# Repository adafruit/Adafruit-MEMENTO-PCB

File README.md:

## Adafruit MEMENTO - Python Programmable DIY Camera PCB

<a href="http://www.adafruit.com/products/5420"><br/>
Click here to purchase one from the Adafruit shop</a>

PCB files for the Adafruit MEMENTO - Python Programmable DIY Camera. 

Format is EagleCAD schematic and board layout
* https://www.adafruit.com/product/5420

### Description

Make memories, or just a cool camera-based project, with Adafruit's MEMENTO Camera Board. It's a development board with everything you need to create programmable camera and vision projects: with a camera module, TFT preview screen, buttons, SD card slot and driven by a powerful ESP32-S3 with 2 MB of PSRAM for buffering 5 MegaPixel camera images.

This product is just the mainboard, and does not come with an enclosure, LED ring, hardware, SD card, or battery.

The ESP32-S3 is a WiFi and Bluetooth LE capable, 240 MHz dual core Tensilica processor - much like the famous ESP32. The S3 adds native USB support so it's great for use with Arduino or CircuitPython. The S3 also has the ability to interface with raw camera modules. The cameras require 12 GPIO pins and fast data transfer in order to get images off the sensor, and then a lot of memory for storing 2560 x 1920 images - which is why we picked an S3 module with 2MB of PSRAM so that we can read JPEGs into memory for saving onto an SD card.

To make the board easy to use we added a ton of supporting hardware, here's a full list of the hardware included:

* ESP32-S3 module with 8 MB Flash, 2 MB PSRAM - dual core 240MHz Tensilica with WiFi and BTLE.
* OV5640 camera module with 72 degree view and auto-focus motor - 5MP camera sensor with JPEG encoder built in.
* 1.54" 240x240 Color TFT - For previewing the camera images, or user interface design.
* MicroSD card slot - Store images or animations to any SPI-capable micro SD card.
* Two Digital/Analog Stemma Ports - JST PH-3 connectors for A0, A1 and power+ground for adding external buttons, LEDs, or sensors. Can provide 3V or 5V power.
* I2C Stemma QT Port - Connect just about any I2C sensor you please with a Stemma QT JST SH port, provides 3.3V power and logic.
* LIS3DH Accelerometer - Triple-access accelerometer can detect orientation, shaking or movement.
* LiPoly battery charging support - Use a 3.7/4.2V 350mA or 420mA battery for on-the-go snaps.
* 6 User Buttons - change modes, preview saved images, play DOOM (?). Connected through a GPIO expander
* Buzzer - play tones or alerts, or indicate when a photo was successfully taken
* Analog Microphone - Can be used as a sensor to detect loud sounds, not for recording video with audio.
* Shutter button - Connected to GPIO 0 for entering the ROM bootloader
* Reset button - For entering the bootloader or starting over
* On/Off switch - Cut all power when using a battery 
* USB Type C for programming the ESP32-S3, as well as REPL access in CircuitPython and charging the optional LiPoly battery
* Breakout pads for hardware UART - for more intense debugging needs, solder wires to the through-hole pads to connect to a console cable.
* Four M3 standoffs for mounting or enclosure attachment.

We've got both Arduino and CircuitPython example code that lets you preview the camera, adjust settings, and take photos that are saved to disk. However, we recommend CircuitPython because the compilation time in Arduino is pretty intense due to the huge amount of code required to run the camera. CircuitPython is fast to develop for and our library will make it easy to start making custom camera projects.

### License

Adafruit invests time and resources providing this open source design, please support Adafruit and open-source hardware by purchasing products from [Adafruit](https://www.adafruit.com)!

Designed by Limor Fried/Ladyada for Adafruit Industries.

Creative Commons Attribution/Share-Alike, all text above must be included in any redistribution. 
See license.txt for additional details.

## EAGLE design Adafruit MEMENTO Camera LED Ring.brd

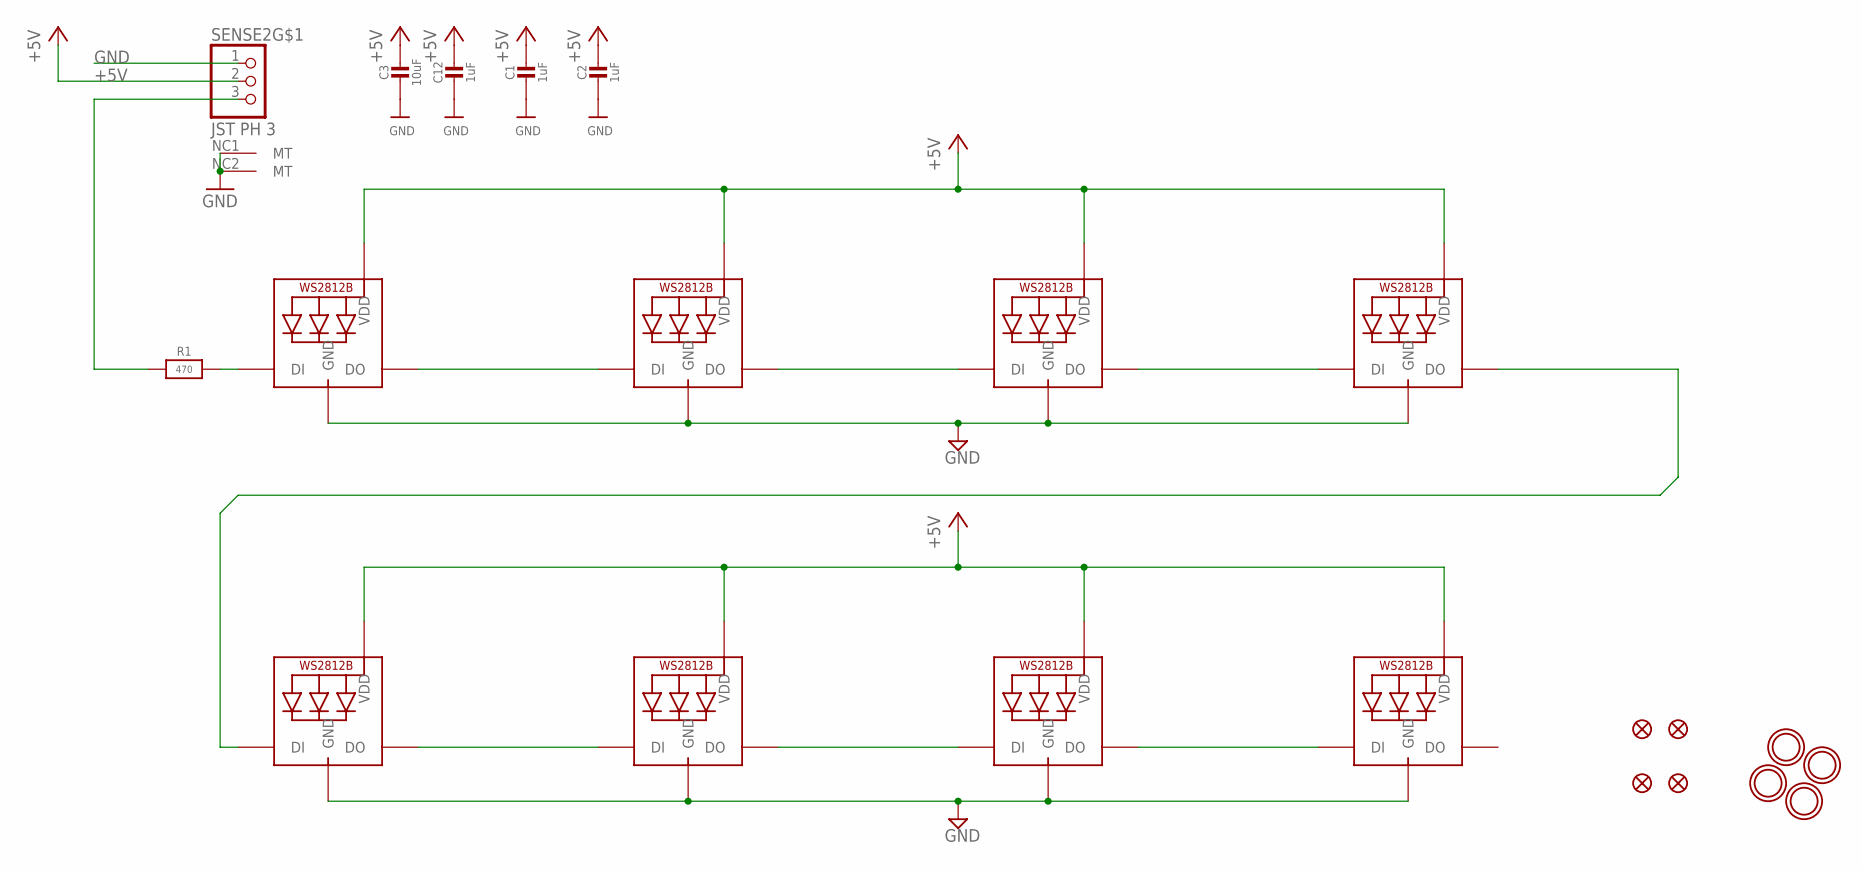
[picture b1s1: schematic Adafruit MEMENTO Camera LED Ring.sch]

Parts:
C1, C2, C12: 1uF; 0603-NO
C3: 10uF; 0805-NO
FID1, FID2, FID3, FID4: FIDUCIAL_1MM
LED1, LED3, LED5, LED7, LED9, LED11, LED13, LED15: WS2812B_5050N; WS2812B-NARROW
R1: 470; 0603-NO
SENSE2: JST PH 3; JSTPH3
U$1, U$2, U$3, U$4: MOUNTINGHOLE3.0THIN; MOUNTINGHOLE_3.0_PLATEDTHIN

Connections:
+5V: C1.1, C2.1, C3.1, C12.1, LED1.1-VDD (VDD), LED3.1-VDD (VDD), LED5.1-VDD (VDD), LED7.1-VDD (VDD), LED9.1-VDD (VDD), LED11.1-VDD (VDD), LED13.1-VDD (VDD), LED15.1-VDD (VDD), SENSE2.2
GND: C1.2, C2.2, C3.2, C12.2, LED1.3-GND (GND), LED3.3-GND (GND), LED5.3-GND (GND), LED7.3-GND (GND), LED9.3-GND (GND), LED11.3-GND (GND), LED13.3-GND (GND), LED15.3-GND (GND), SENSE2.1, SENSE2.NC1 (MT), SENSE2.NC2 (MT)
IN: R1.1, SENSE2.3
unnamed: LED1.2-DOUT (DO), LED3.4-DIN (DI)
unnamed: LED3.2-DOUT (DO), LED5.4-DIN (DI)
unnamed: LED5.2-DOUT (DO), LED7.4-DIN (DI)
unnamed: LED9.2-DOUT (DO), LED11.4-DIN (DI)
unnamed: LED11.2-DOUT (DO), LED13.4-DIN (DI)
unnamed: LED13.2-DOUT (DO), LED15.4-DIN (DI)
unnamed: LED7.2-DOUT (DO), LED9.4-DIN (DI)
unnamed: LED1.4-DIN (DI), R1.2

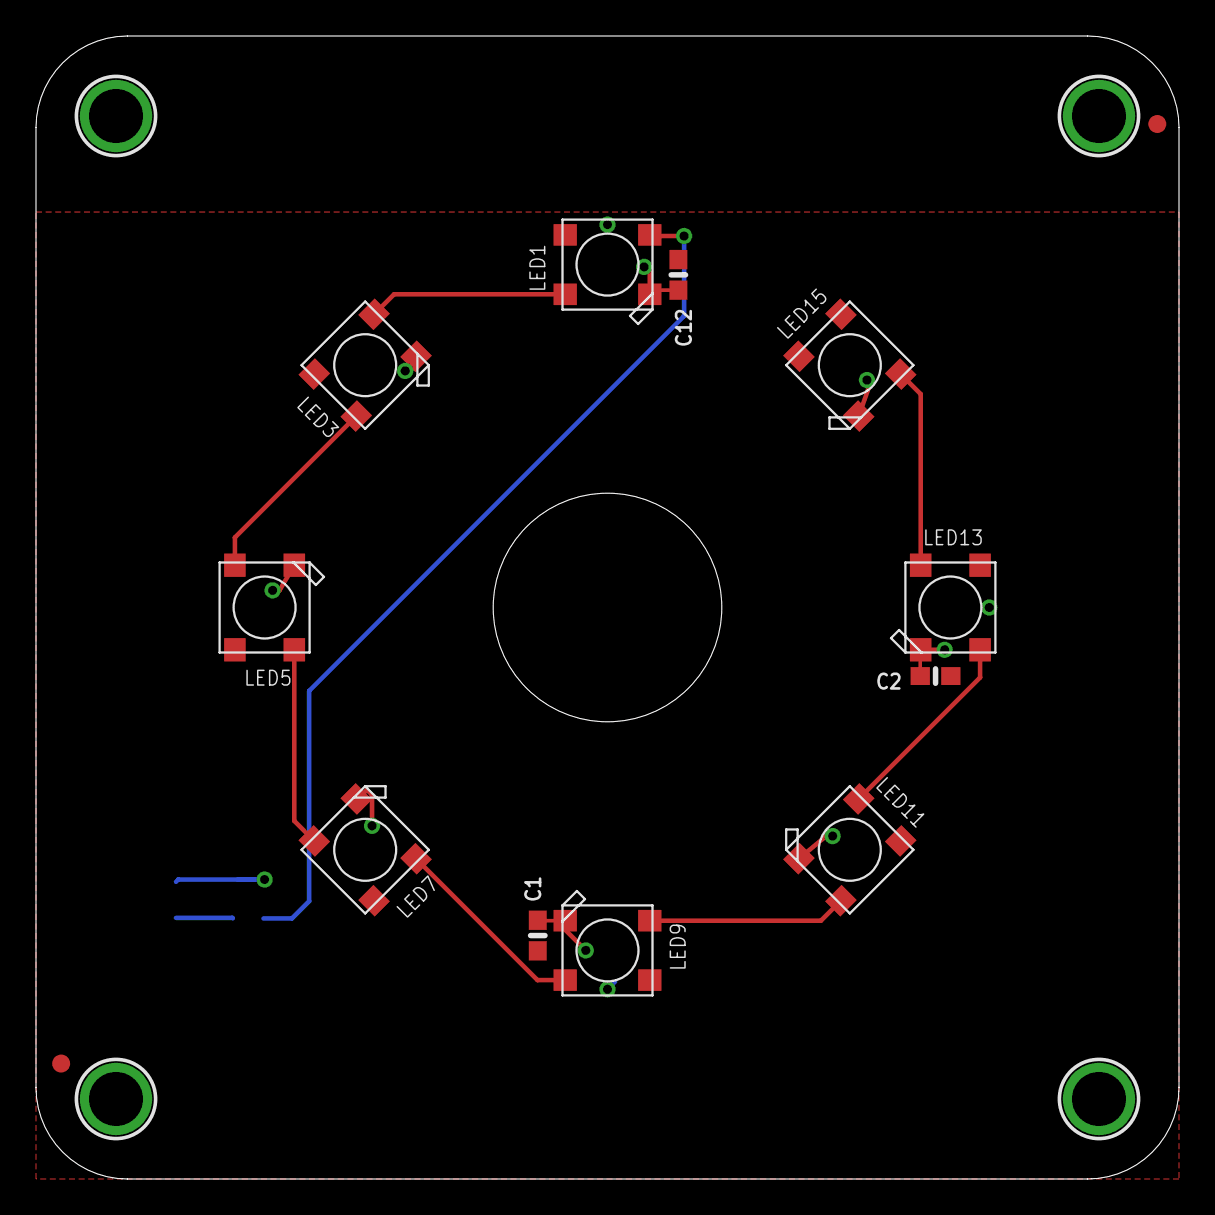
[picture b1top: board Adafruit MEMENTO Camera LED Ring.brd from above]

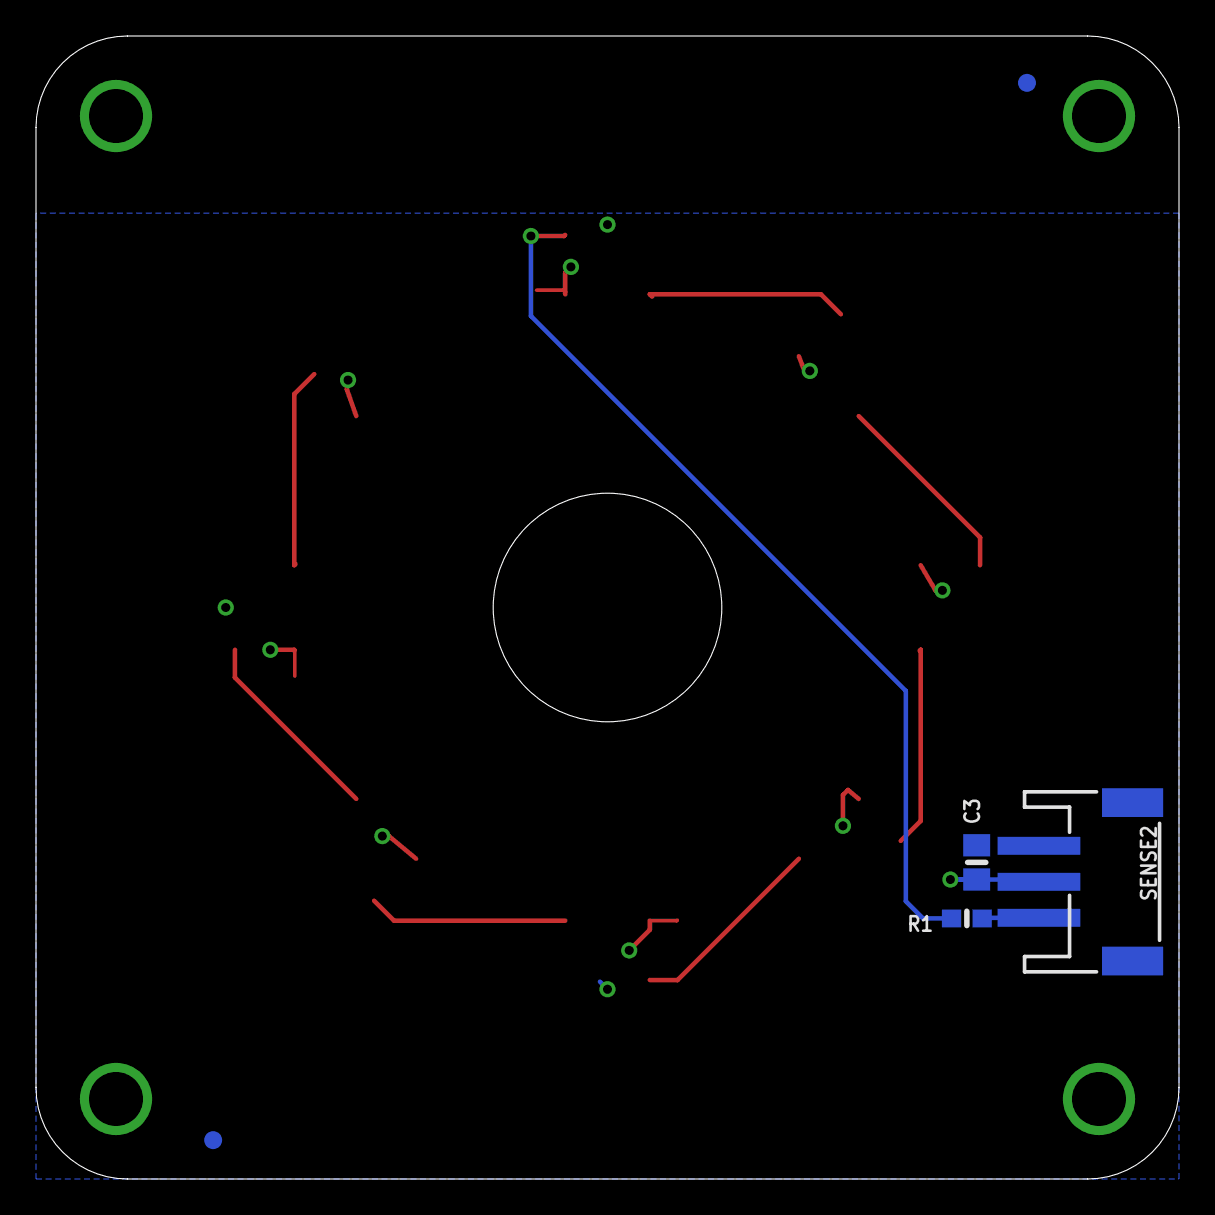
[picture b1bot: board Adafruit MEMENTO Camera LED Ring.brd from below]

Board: 2 copper layers, 63.5 x 63.5 mm, 24 parts (6 on the bottom side), 11 nets.

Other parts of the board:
U$8: MEMENTO_LED_BOT
U$9: MEMENTO_LED_TOP

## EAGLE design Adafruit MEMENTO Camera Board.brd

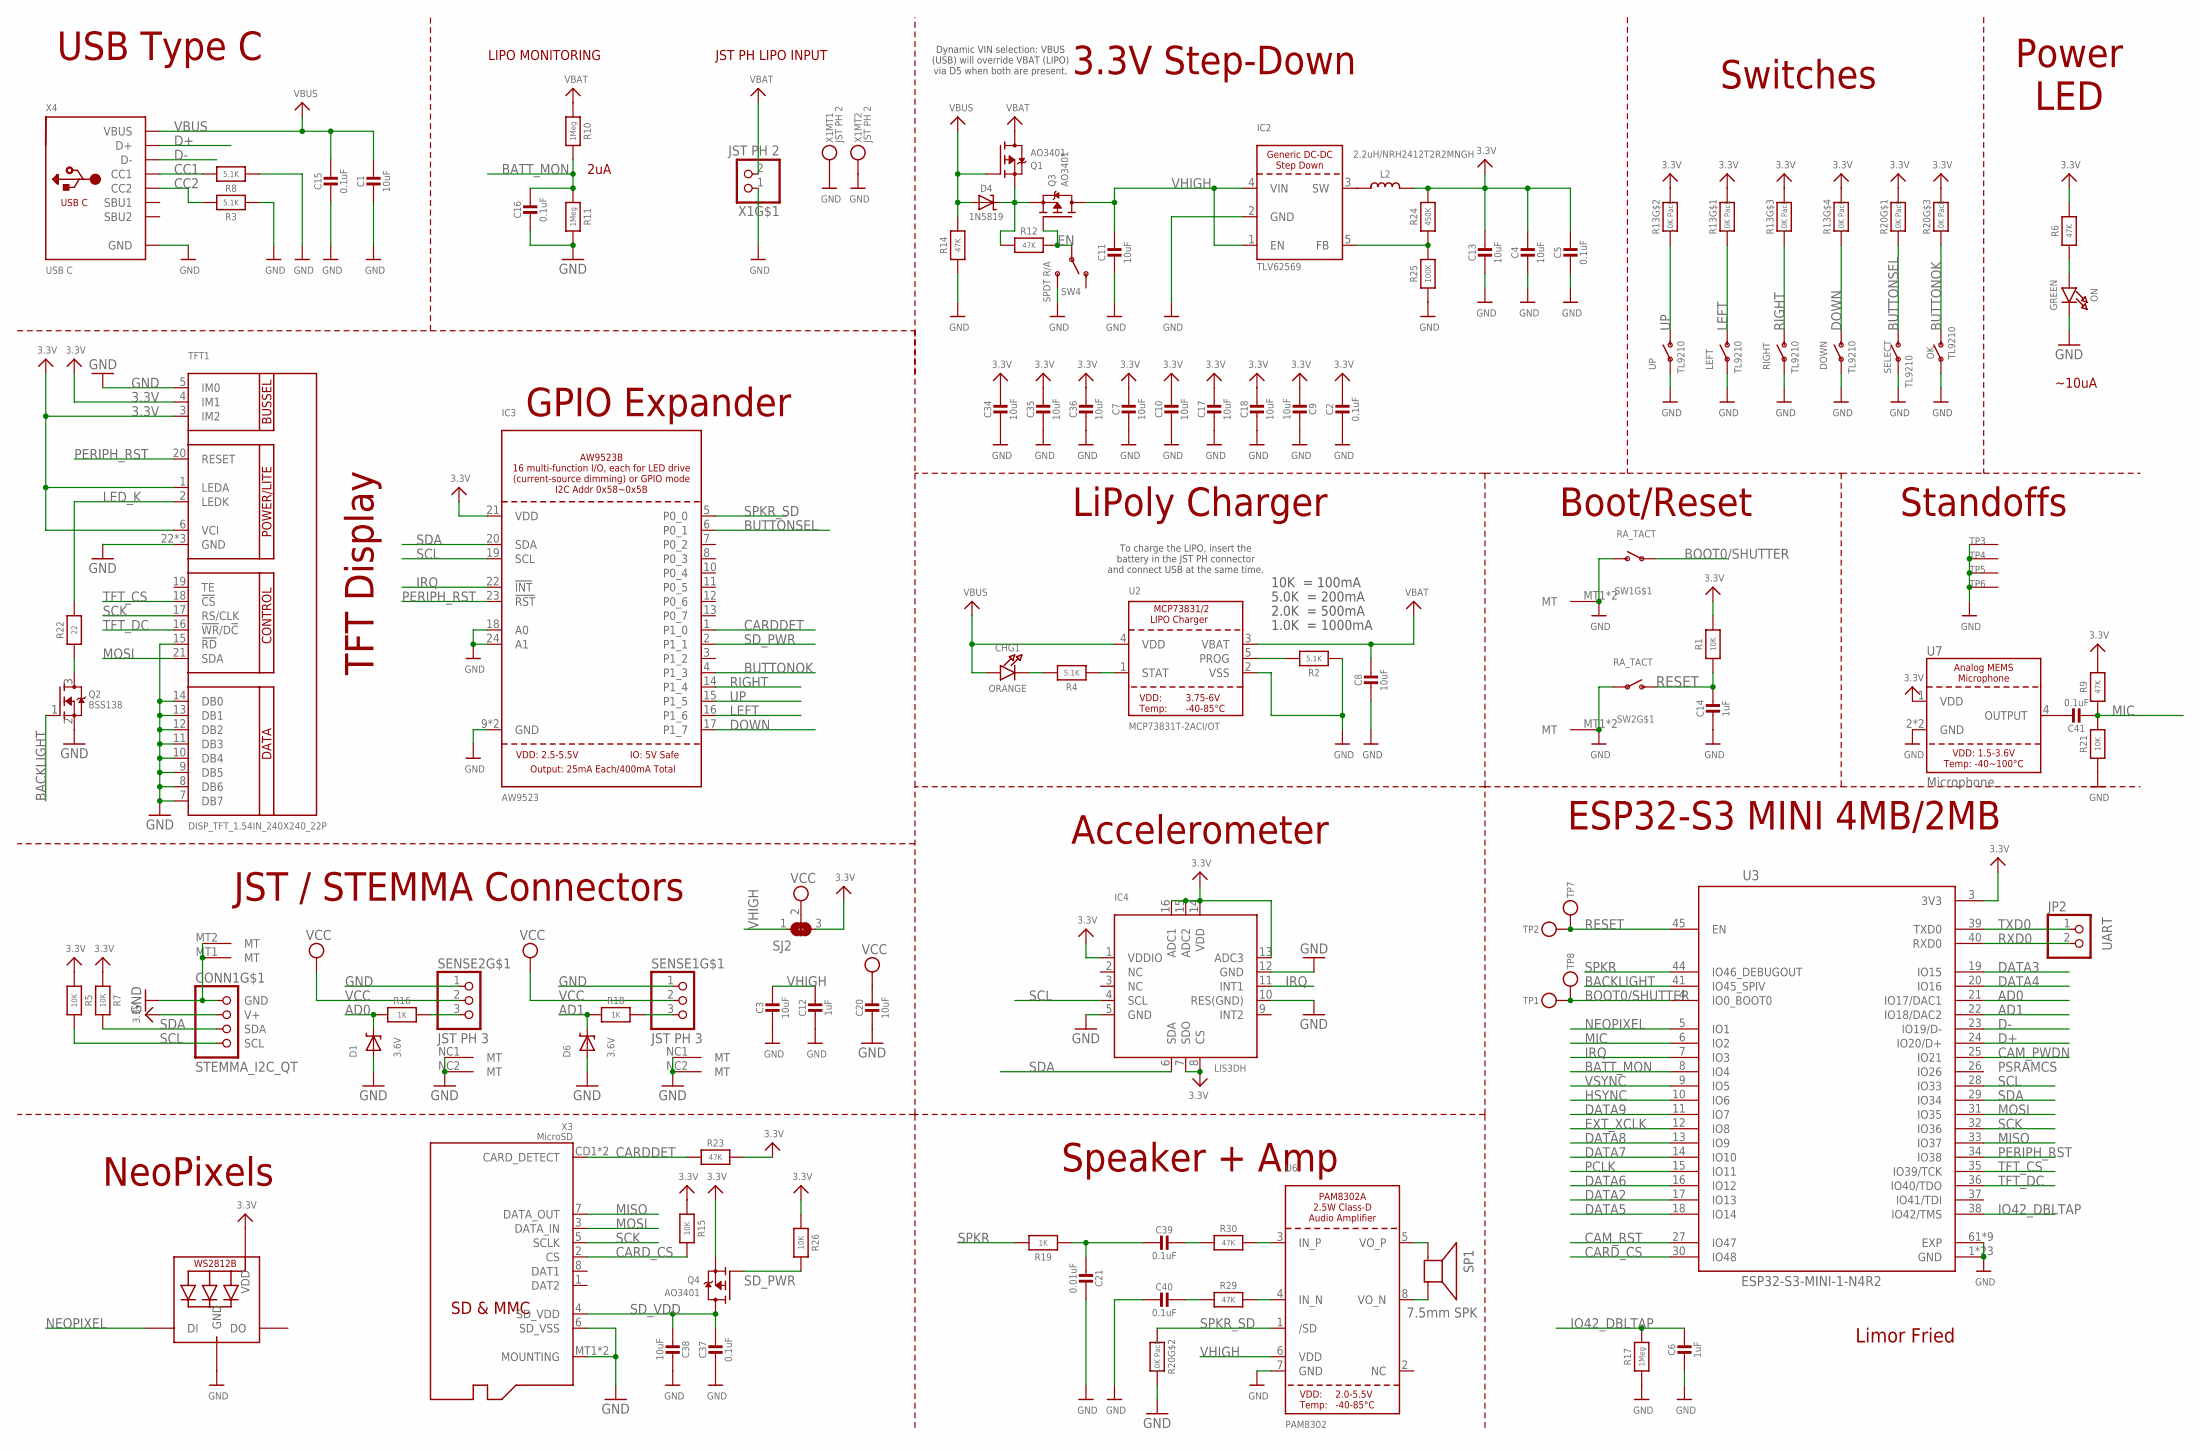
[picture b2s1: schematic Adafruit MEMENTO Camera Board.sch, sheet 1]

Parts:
C1, C3, C4, C7, C8, C9, C10, C11, C13, C17, C18, C20, C34, C35, C36, C38: 10uF; 0805-NO
C2, C5, C15, C16, C37, C39, C40, C41: 0.1uF; 0603-NO
C6, C12, C14: 1uF; 0603-NO
C21: 0.01uF; 0603-NO
CHG1: ORANGE; CHIPLED_0603_NOOUTLINE
CONN1: STEMMA_I2C_QT; JST_SH4
D1, D6: 3.6V; SOD-323
D4: 1N5819; SOD-123
DOWN: TL9210
IC2: TLV62569; SOT23-5
IC3: AW9523; QFN24_4MM_SMSC
IC4: LIS3DH; LGA16_3X3MM
JP2: UART; 1X02_ROUND
L2: 2.2uH/NRH2412T2R2MNGH; INDUCTOR_TAIYOYUDEN_NR3015
LED2: WS2812B_SK6805_1515; SK6805_1515
LEFT: TL9210
OK: TL9210
ON: GREEN; CHIPLED_0603_NOOUTLINE
Q1, Q3, Q4: AO3401; SOT23-R
Q2: BSS138; SOT23-WIDE
R1, R5, R7, R15, R21, R26: 10K; 0603-NO
R2, R3, R4, R8: 5.1K; 0603-NO
R6, R9, R12, R14, R23, R29, R30: 47K; 0603-NO
R10, R11, R17: 1Meg; 0603-NO
R13, R20: 10K Pack; RESPACK_4X0603
R16, R18, R19: 1K; 0603-NO
R22: 22; 0603-NO
R24: 450K; 0603-NO
R25: 100K; 0603-NO
RIGHT: TL9210
SELECT: TL9210
SENSE1, SENSE2: JST PH 3; JSTPH3
SJ2: SOLDERJUMPER_2WAY; SOLDERJUMPER_2WAY_OPEN_NOPASTE
SP1: 7.5mm SPK; BUZZER_SMT_7.5MM
SW1, SW2: RA_TACT; SPST_TACTILE_RA
SW4: SPDT R/A; SPDT_SMT_SSSS811101
TFT1: DISP_TFT_1.54IN_240X240_22P; TFT_1.54IN_240X240_22PIN
TP1, TP2, TP7, TP8: TESTPOINTROUND1.5MMNO; TESTPOINT_ROUND_1.5MM_NO
TP3, TP4, TP5, TP6: SEWTAP_SMTNUTM3; SMT_NUT_3MM
U2: MCP73831T-2ACI/OT; SOT23-5
U3: ESP32-S3-MINI-1-N4R2; ESP32-S2-MINI-1
U6: PAM8302; MSOP8_0.65MM
U7: Microphone; MEMS_MIC_2.75X1.85
UP: TL9210
X1: JST PH 2; JSTPH2_BATT
X3: MicroSD; MICROSD
X4: USB C; USB_C_CUSB31-CFM2AX-01-X

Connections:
3.3V: C2.1, C4.1, C5.1, C7.1, C9.2, C10.1, C13.1, C17.1, C18.1, C34.1, C35.1, C36.1, CONN1.2 (V+), IC3.21 (VDD), IC4.1 (VDDIO), IC4.7 (SDO), IC4.8 (CS), IC4.13 (ADC3), IC4.14 (VDD), IC4.15 (ADC2), IC4.16 (ADC1), L2.P$2 (2), LED2.2 (VDD), Q4.2 (S), R1.2, R5.1, R6.2, R7.1, R9.2, R13.5 (2), R13.6 (2), R13.7 (2), R13.8 (2), R15.2, R20.6 (2), R20.8 (2), R23.2, R24.2, R26.1, SJ2.3, TFT1.1 (LEDA), TFT1.3 (IM2), TFT1.4 (IM1), TFT1.6 (VCI), U3.3 (3V3), U7.1 (VDD); also elsewhere on the board
A1_JST1: R18.1, SENSE1.3
AD0: D1.C, R16.2, U3.21 (IO17/DAC1)
AD1: D6.C, R18.2, U3.22 (IO18/DAC2)
BACKLIGHT: Q2.1 (G), U3.41 (IO45_SPIV)
BATT_MON: C16.1, R10.2, R11.1, U3.8 (IO4)
BOOT0/SHUTTER: SW1.1, TP1.P$1, TP8.P$1, U3.4 (IO0_BOOT0)
BUTTONOK: IC3.4 (P1_3), OK.2 (S), R20.3 (1)
BUTTONSEL: IC3.6 (P0_1), R20.1, SELECT.2 (S)
CAM_PWDN: U3.25 (IO21); also elsewhere on the board
CAM_RST: U3.27 (IO47); also elsewhere on the board
CARDDET: IC3.1 (P1_0), R23.1, X3.CD1 (CARD_DETECT), X3.CD2 (CARD_DETECT)
CARD_CS: R15.1, U3.30 (IO48), X3.2 (CS)
CC1: R8.2, X4.A5 (CC1)
CC2: R3.2, X4.B5 (CC2)
D10_JST: R16.1, SENSE2.3
D+: U3.24 (IO20/D+), X4.A6 (D+), X4.B6 (D+)
D-: U3.23 (IO19/D-), X4.A7 (D-), X4.B7 (D-)
DATA2: U3.17 (IO13); also elsewhere on the board
DATA3: U3.19 (IO15); also elsewhere on the board
DATA4: U3.20 (IO16); also elsewhere on the board
DATA5: U3.18 (IO14); also elsewhere on the board
DATA6: U3.16 (IO12); also elsewhere on the board
DATA7: U3.14 (IO10); also elsewhere on the board
DATA8: U3.13 (IO9); also elsewhere on the board
DATA9: U3.11 (IO7); also elsewhere on the board
DOWN: DOWN.2 (S), IC3.17 (P1_7), R13.4 (1)
EN: Q3.1 (G), R12.2, SW4.B
EXT_XCLK: U3.12 (IO8); also elsewhere on the board
FB: IC2.5 (FB), R24.1, R25.2
GND: C1.2, C2.2, C3.2, C4.2, C5.2, C6.2, C7.2, C8.2, C9.1, C10.2, C11.2, C12.2, C13.2, C14.2, C15.2, C16.2, C17.2, C18.2, C20.2, C21.1, C34.2, C35.2, C36.2, C37.2, C38.1, C40.2, CONN1.1 (GND), CONN1.MT1 (MT), CONN1.MT2 (MT), D1.A, D6.A, DOWN.1, IC2.2 (GND), IC3.9 (GND), IC3.18 (A0), IC3.24 (A1), IC3.THERM (GND), IC4.5 (GND), IC4.10 (RES(GND)), IC4.12 (GND), LED2.4 (GND), LEFT.1, OK.1, ON.C, Q2.2 (S), R2.1, R3.1, R8.1, R11.2, R14.1, R17.1, R20.7 (2), R21.1, R25.1, RIGHT.1, SELECT.1, SENSE1.1, SENSE1.NC1 (MT), SENSE1.NC2 (MT), SENSE2.1, SENSE2.NC1 (MT), SENSE2.NC2 (MT), SW1.2 (S), SW1.MT1 (MT), SW1.MT2 (MT), SW2.1, SW2.MT1 (MT), SW2.MT2 (MT), SW4.C (S), TFT1.5 (IM0), TFT1.7 (DB7), TFT1.8 (DB6), TFT1.9 (DB5), TFT1.10 (DB4), TFT1.11 (DB3), TFT1.12 (DB2), TFT1.13 (DB1), TFT1.14 (DB0), TFT1.15 (!RD), TFT1.22 (GND), TFT1.SUPPORT1 (GND), TFT1.SUPPORT2 (GND), TP3.P$1, TP4.P$1, TP5.P$1, TP6.P$1, U2.2 (VSS), U3.1 (GND), U3.2 (GND), U3.42 (GND), U3.43 (GND), U3.46 (GND), U3.47 (GND), U3.48 (GND), U3.49 (GND), U3.50 (GND), U3.51 (GND), U3.52 (GND), U3.53 (GND), U3.54 (GND), U3.55 (GND), U3.56 (GND), U3.57 (GND), U3.58 (GND), U3.59 (GND), U3.60 (GND), U3.61 (EXP), U3.62 (GND), U3.63 (GND), U3.64 (GND), U3.65 (GND), U3.66 (EXP), U3.67 (EXP), U3.68 (EXP), U3.69 (EXP), U3.70 (EXP), U3.71 (EXP), U3.72 (EXP), U3.73 (EXP), U6.7 (GND), U7.2 (GND), U7.3 (GND), UP.1, X1.1, X1.NC1, X1.NC2, X3.6 (SD_VSS), X3.MT1 (MOUNTING), X3.MT2 (MOUNTING), X4.A1B12 (GND), X4.B1A12 (GND); also elsewhere on the board
HSYNC: U3.10 (IO6); also elsewhere on the board
IO42_DBLTAP: C6.1, R17.2, U3.38 (IO42/TMS)
IRQ: IC3.22 (!INT), IC4.11 (INT1), U3.7 (IO3)
LED_K: R22.1, TFT1.2 (LEDK)
LEFT: IC3.16 (P1_6), LEFT.2 (S), R13.1
MIC: C41.2, R9.1, R21.2, U3.6 (IO2)
MISO: U3.33 (IO37), X3.7 (DATA_OUT)
MOSI: TFT1.21 (SDA), U3.31 (IO35), X3.3 (DATA_IN)
unnamed: C41.1, U7.4 (OUTPUT)
unnamed: ON.A, R6.1
unnamed: R4.1, U2.1 (STAT)
unnamed: Q2.3 (D), R22.2
unnamed: CHG1.C, R4.2
unnamed: R29.2, U6.4 (IN_N)
unnamed: R30.2, U6.3 (IN_P)
unnamed: R2.2, U2.5 (PROG)
unnamed: C40.1, R29.1
unnamed: SP1.-, U6.8 (VO_N)
unnamed: SP1.+, U6.5 (VO_P)
unnamed: C39.1, R30.1
unnamed: C21.2, C39.2, R19.1
unnamed: IC2.3 (SW), L2.P$1 (1)
unnamed: D4.C, Q1.2 (S), Q3.2 (S), R12.1
NEOPIXEL: LED2.1 (DI), U3.5 (IO1)
PCLK: U3.15 (IO11); also elsewhere on the board
PERIPH_RST: IC3.23 (!RST), TFT1.20 (RESET), U3.34 (IO38)
RESET: C14.1, R1.1, SW2.2 (S), TP2.P$1, TP7.P$1, U3.45 (EN)
RIGHT: IC3.14 (P1_4), R13.3 (1), RIGHT.2 (S)
RXD0: JP2.2, U3.40 (RXD0)
SCK: TFT1.17 (RS/CLK), U3.32 (IO36), X3.5 (SCLK)
SCL: CONN1.4 (SCL), IC3.19 (SCL), IC4.4 (SCL), R5.2, U3.28 (IO33); also elsewhere on the board
SDA: CONN1.3 (SDA), IC3.20 (SDA), IC4.6 (SDA), R7.2, U3.29 (IO34); also elsewhere on the board
SD_PWR: IC3.2 (P1_1), Q4.1 (G), R26.2
SD_VDD: C37.1, C38.2, Q4.3 (D), X3.4 (SD_VDD)
SPKR: R19.2, U3.44 (IO46_DEBUGOUT)
SPKR_SD: IC3.5 (P0_0), R20.2 (1), U6.1 (/SD)
TFT_CS: TFT1.18 (!CS), U3.35 (IO39/TCK)
TFT_DC: TFT1.16 (!WR!/D!C), U3.36 (IO40/TDO)
TXD0: JP2.1, U3.39 (TXD0)
UP: IC3.15 (P1_5), R13.2 (1), UP.2 (S)
VBAT: C8.1, Q1.3 (D), R10.1, U2.3 (VBAT), X1.2
VBUS: C1.1, C15.1, CHG1.A, D4.A, Q1.1 (G), R14.2, U2.4 (VDD), X4.A4B9 (VBUS), X4.B4A9 (VBUS)
VCC: C20.1, SENSE1.2, SENSE2.2, SJ2.2
VHIGH: C3.1, C11.1, C12.1, IC2.1 (EN), IC2.4 (VIN), Q3.3 (D), SJ2.1, U6.6 (VDD); also elsewhere on the board
VSYNC: U3.9 (IO5); also elsewhere on the board

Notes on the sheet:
Limor Fried
10K = 100mA
5.0K = 200mA
2.0K = 500mA
1.0K = 1000mA
LIPO MONITORING
To charge the LIPO, insert the battery in the JST PH connector and connect USB at the same time.
JST PH LIPO INPUT
Dynamic VIN selection: VBUS (USB) will override VBAT (LIPO) via D5 when both are present.
PSRAMCS
2uA
~10uA
TFT Display
LiPoly Charger
Accelerometer
Speaker + Amp
3.3V Step-Down
ESP32-S3 MINI 4MB/2MB
Switches
Boot/Reset
USB Type C
Power LED
NeoPixels
JST / STEMMA Connectors
Standoffs
GPIO Expander

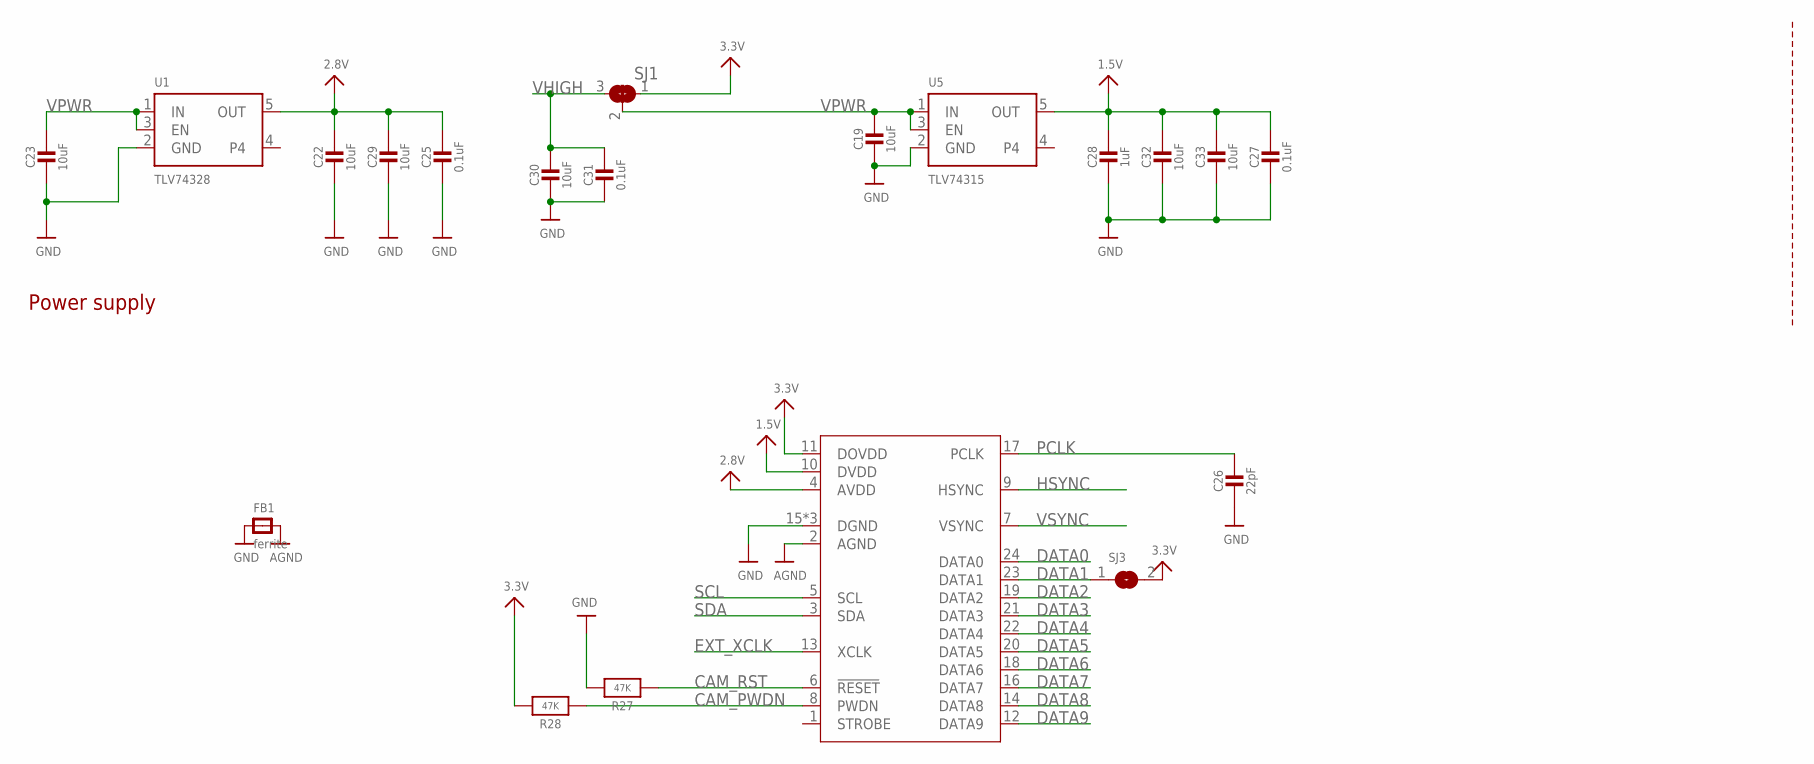
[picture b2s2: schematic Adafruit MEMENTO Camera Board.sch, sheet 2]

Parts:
C19, C22, C23, C29, C30, C32, C33: 10uF; 0805-NO
C25, C27, C31: 0.1uF; 0603-NO
C26: 22pF; 0603-NO
C28: 1uF; 0603-NO
FB1: ferrite; 0603-NO
R27, R28: 47K; 0603-NO
SJ1: SOLDERJUMPER_2WAY; SOLDERJUMPER_2WAY_OPEN_NOPASTE
SJ3: SOLDERJUMPERCLOSED; SOLDERJUMPER_CLOSEDWIRE
U1: TLV74328; SOT23-5; JLC_ROTATION 0
U5: TLV74315; SOT23-5; JLC_ROTATION 0
X2: CAMERA_OV2640; OV2640FSL

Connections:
1.5V: C27.1, C28.1, C32.1, C33.1, U5.5 (OUT), X2.10 (DVDD)
2.8V: C22.1, C25.1, C29.1, U1.5 (OUT), X2.4 (AVDD)
3.3V: R28.2, SJ1.1, SJ3.2, X2.11 (DOVDD); also elsewhere on the board
AGND: FB1.2, X2.2 (AGND)
CAM_PWDN: R28.1, X2.8 (PWDN); also elsewhere on the board
CAM_RST: R27.1, X2.6 (!RESET); also elsewhere on the board
DATA0: X2.24 (DATA0)
DATA1: SJ3.1, X2.23 (DATA1)
DATA2: X2.19 (DATA2); also elsewhere on the board
DATA3: X2.21 (DATA3); also elsewhere on the board
DATA4: X2.22 (DATA4); also elsewhere on the board
DATA5: X2.20 (DATA5); also elsewhere on the board
DATA6: X2.18 (DATA6); also elsewhere on the board
DATA7: X2.16 (DATA7); also elsewhere on the board
DATA8: X2.14 (DATA8); also elsewhere on the board
DATA9: X2.12 (DATA9); also elsewhere on the board
EXT_XCLK: X2.13 (XCLK); also elsewhere on the board
GND: C19.2, C22.2, C23.2, C25.2, C26.2, C27.2, C28.2, C29.2, C30.2, C31.2, C32.2, C33.2, FB1.1, R27.2, U1.2 (GND), U5.2 (GND), X2.15 (DGND), X2.SPRT1 (DGND), X2.SPRT2 (DGND); also elsewhere on the board
HSYNC: X2.9 (HSYNC); also elsewhere on the board
PCLK: C26.1, X2.17 (PCLK); also elsewhere on the board
SCL: X2.5 (SCL); also elsewhere on the board
SDA: X2.3 (SDA); also elsewhere on the board
VHIGH: C30.1, C31.1, SJ1.3; also elsewhere on the board
VPWR: C19.1, C23.1, SJ1.2, U1.1 (IN), U1.3 (EN), U5.1 (IN), U5.3 (EN)
VSYNC: X2.7 (VSYNC); also elsewhere on the board

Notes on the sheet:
Power supply

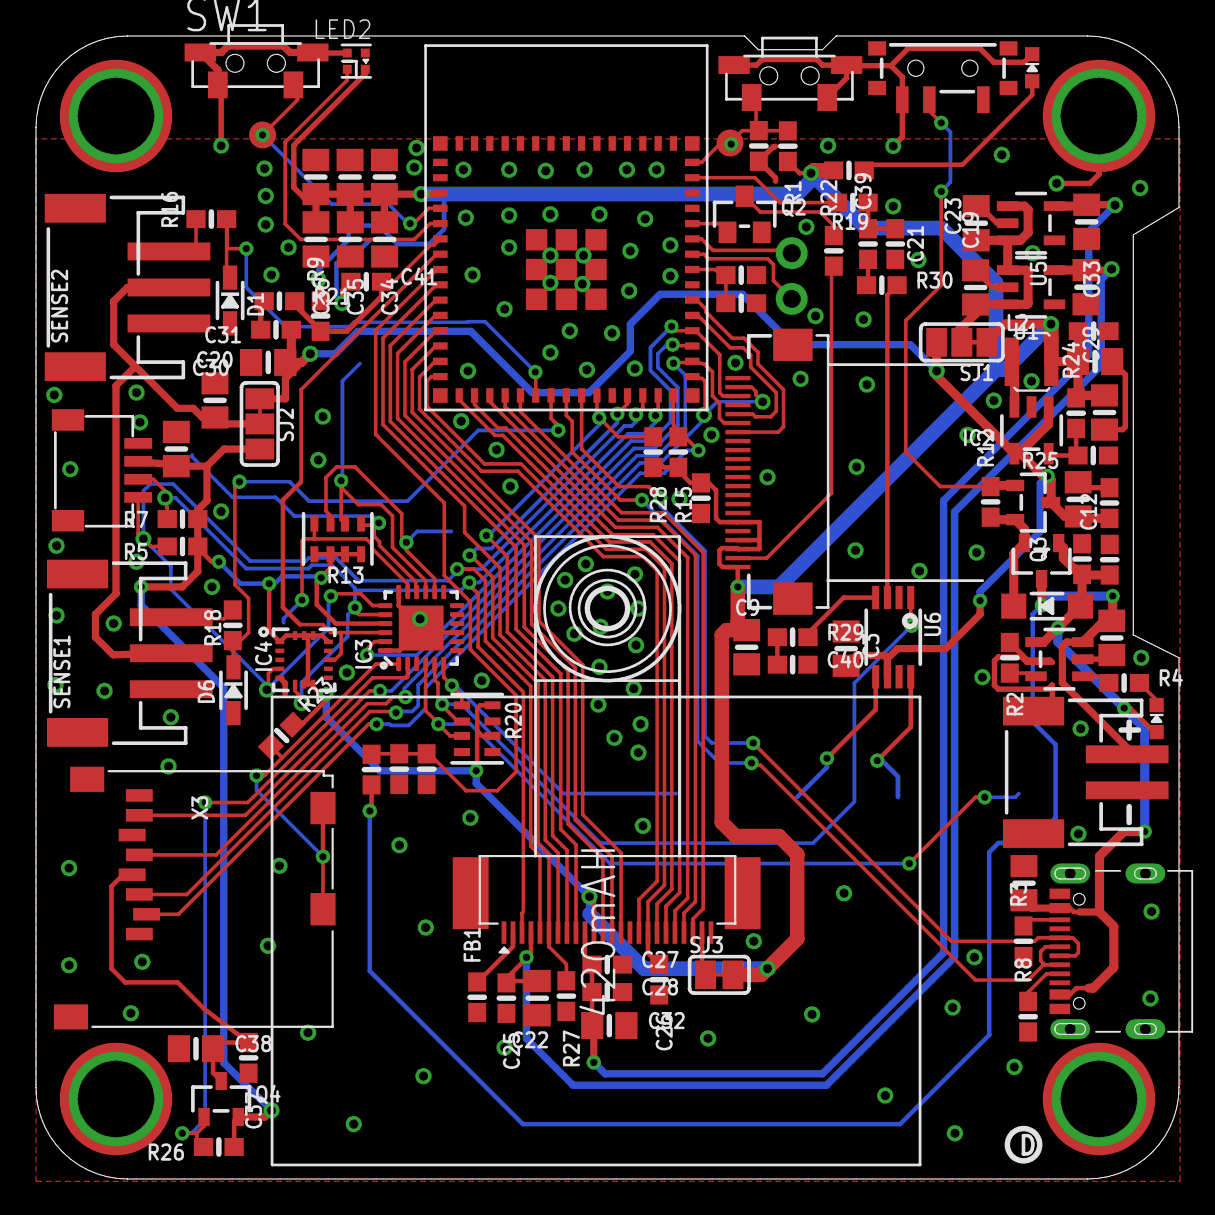
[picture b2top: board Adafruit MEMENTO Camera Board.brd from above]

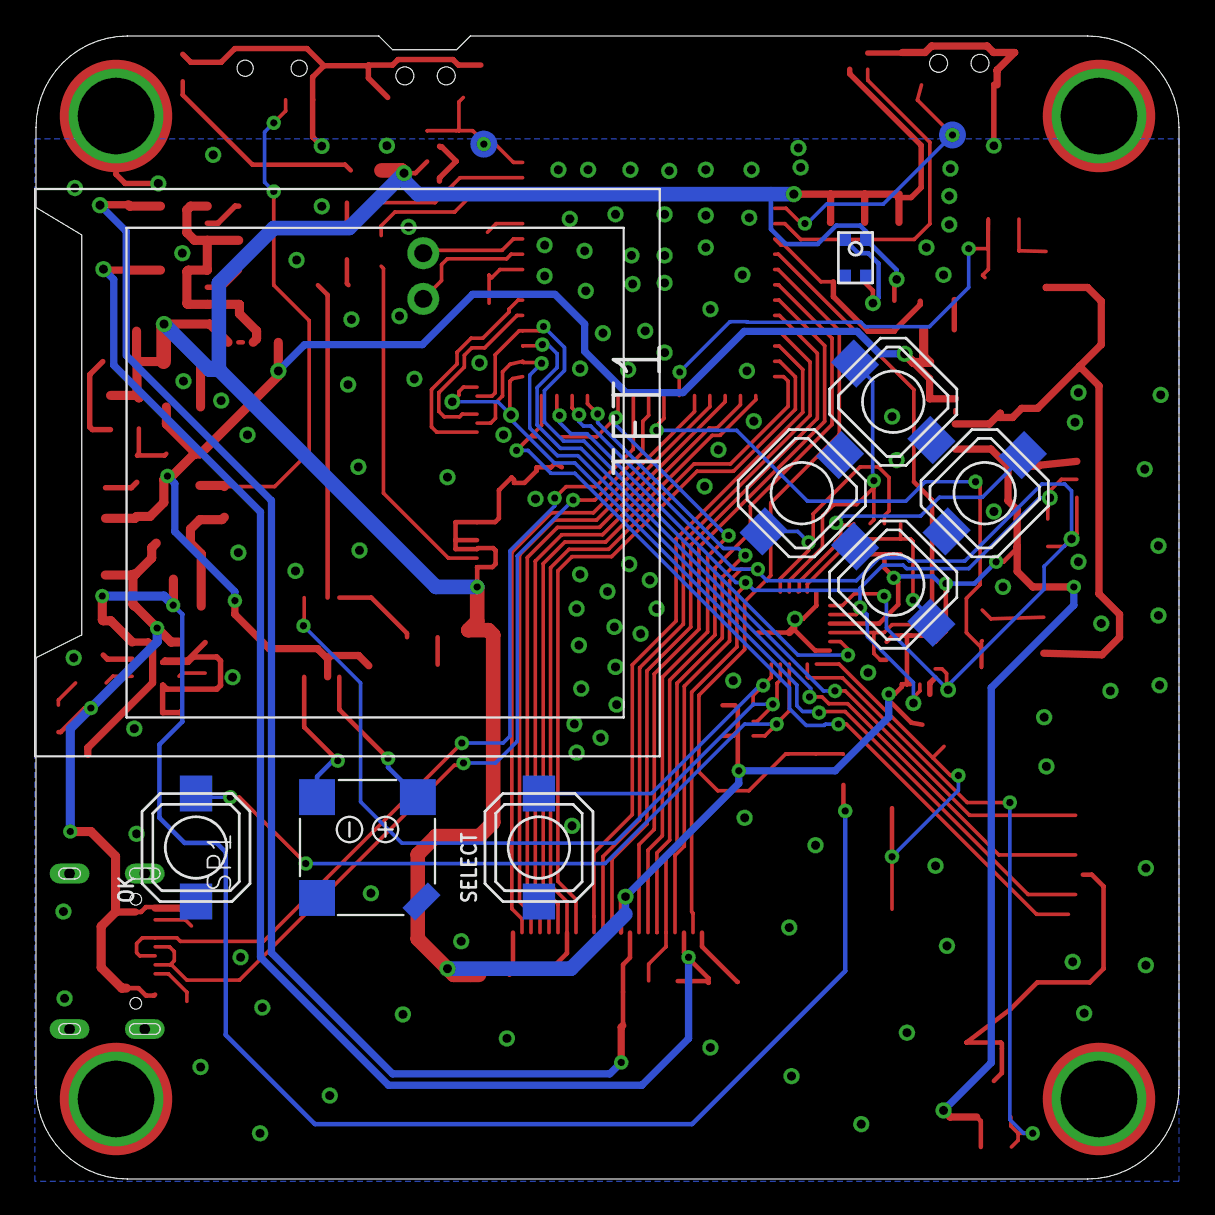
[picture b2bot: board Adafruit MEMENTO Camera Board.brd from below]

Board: 2 copper layers, 63.5 x 63.5 mm, 125 parts (12 on the bottom side), 81 nets.

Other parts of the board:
U$83: LIPO_552535
U$119: MEMENTO_TOP
U$120: MEMENTO_BOT
U$121: PCBFEAT-REV-040

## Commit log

2023-12-14 adding cookiecutter output
2023-12-18 factory reset uf2 and bin
2023-12-21 adding led ring and backplate

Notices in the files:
parts and their libraries:
microbuilder: This work is placed in the public domain, and may be freely used for commercial and non-commercial work with the following conditions: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
COPYRIGHT: Copyright (C) 2018 Accelerated Designs. All rights reserved
